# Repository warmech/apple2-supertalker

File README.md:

# Supertalker - A Speech Digitizer for the Apple II

The Supertalker is a speech digitizer card for the Apple II by Mountain Computer, Inc. Originally produced in 1979 (and subsequently for the PC in the 1980s), the Supertalker is capable of digitizing and playing back speech at any of four bitrates: 0.5 KBps, 1 KBps, 2 KBps, and 4 KBps. The kit originally included a microphone and enclosed (in woodgrain, no less) speaker for use with the card.

This card is somewhat hard to find now, but I happened to come across one at a recent retrocomputing meetup for a few bucks (not knowing what it was other than some cursory googling at the time) and wanted to preserve it. The included manual and disk images are care of [apple2.org](https://mirrors.apple2.org.za/Apple%20II%20Documentation%20Project/Interface%20Cards/Speech/Mountain%20Computer%20Supertalker/).

More details to follow once initial assembly and testing are completed.

## Errata

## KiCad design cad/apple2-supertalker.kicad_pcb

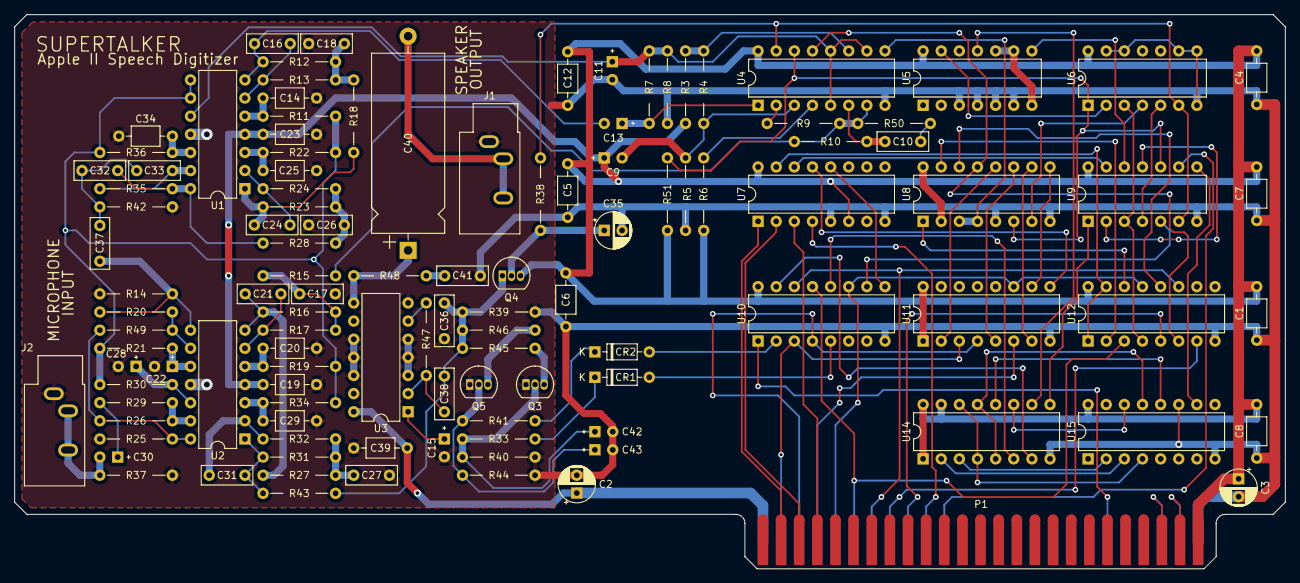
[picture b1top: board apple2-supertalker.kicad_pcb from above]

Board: 2 copper layers, 178.0 x 77.6 mm, 114 parts (0 on the bottom side), 106 nets.

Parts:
C1, C4, C5, C6, C7, C8, C12, C14, C19, C20, C23, C25, C29, C34, C39: 0.1uF 50V; C_Axial_L3.8mm_D2.6mm_P7.50mm_Horizontal
C2, C3, C35: 10uF 35V; CP_Radial_D5.0mm_P2.50mm
C9: 0.39uF 50V; CP_Radial_Tantal_D4.5mm_P2.50mm
C10: 0.068uF 63V; C_Rect_L7.0mm_W2.5mm_P5.00mm
C11, C13, C15, C22, C28, C30, C42, C43: 10uF 25V; CP_Radial_Tantal_D4.5mm_P2.50mm
C16, C31: 0.0015uF 100V; C_Rect_L7.0mm_W2.5mm_P5.00mm
C17, C18, C26, C27, C32, C33, C37, C38, C41: 0.01uF 100V; C_Rect_L7.0mm_W2.5mm_P5.00mm
C21, C24: 82pF 500V; C_Rect_L7.0mm_W2.5mm_P5.00mm
C36: 100pF 500V; C_Rect_L7.0mm_W2.5mm_P5.00mm
C40: 470uF 25V; CP_Axial_L25.0mm_D10.0mm_P30.00mm_Horizontal
CR1, CR2: 1N4148; D_DO-35_SOD27_P7.62mm_Horizontal
J1: SPKR OUTPUT; Jack_3.5mm_CUI_SJ1-3533NG_Horizontal
J2: MIC INPUT; Jack_3.5mm_CUI_SJ1-3533NG_Horizontal
P1: Apple II Expansion Bus; Apple_II_Expansion_Bus_Card_Edge
Q3, Q4, Q5: PN2222A; TO-92_Inline
R3: 3.3K; R_Axial_DIN0207_L6.3mm_D2.5mm_P10.16mm_Horizontal
R4: 18K; R_Axial_DIN0207_L6.3mm_D2.5mm_P10.16mm_Horizontal
R5: 2.7M; R_Axial_DIN0207_L6.3mm_D2.5mm_P10.16mm_Horizontal
R6: 1.3K; R_Axial_DIN0207_L6.3mm_D2.5mm_P10.16mm_Horizontal
R7, R9: 620; R_Axial_DIN0207_L6.3mm_D2.5mm_P10.16mm_Horizontal
R8, R29, R37, R49, R51: 1K; R_Axial_DIN0207_L6.3mm_D2.5mm_P10.16mm_Horizontal
R10, R38: 4.7K; R_Axial_DIN0207_L6.3mm_D2.5mm_P10.16mm_Horizontal
R11, R14, R19, R21, R22, R25, R30, R33, R34, R36, R41: 10K; R_Axial_DIN0207_L6.3mm_D2.5mm_P10.16mm_Horizontal
R12, R18, R27, R31, R42: 20K; R_Axial_DIN0207_L6.3mm_D2.5mm_P10.16mm_Horizontal
R13, R32: 33K; R_Axial_DIN0207_L6.3mm_D2.5mm_P10.16mm_Horizontal
R15, R16, R23, R28: 51K; R_Axial_DIN0207_L6.3mm_D2.5mm_P10.16mm_Horizontal
R17, R24, R43: 62K; R_Axial_DIN0207_L6.3mm_D2.5mm_P10.16mm_Horizontal
R20: 22K; R_Axial_DIN0207_L6.3mm_D2.5mm_P10.16mm_Horizontal
R26: 15K; R_Axial_DIN0207_L6.3mm_D2.5mm_P10.16mm_Horizontal
R35: 150K; R_Axial_DIN0207_L6.3mm_D2.5mm_P10.16mm_Horizontal
R39: 9.1K; R_Axial_DIN0207_L6.3mm_D2.5mm_P10.16mm_Horizontal
R40, R44: 6.2K; R_Axial_DIN0207_L6.3mm_D2.5mm_P10.16mm_Horizontal
R45: 2.2K; R_Axial_DIN0207_L6.3mm_D2.5mm_P10.16mm_Horizontal
R46: 6.8K; R_Axial_DIN0207_L6.3mm_D2.5mm_P10.16mm_Horizontal
R47: 470K; R_Axial_DIN0207_L6.3mm_D2.5mm_P10.16mm_Horizontal
R48: 2.7K; R_Axial_DIN0207_L6.3mm_D2.5mm_P10.16mm_Horizontal
R50: 68; R_Axial_DIN0207_L6.3mm_D2.5mm_P10.16mm_Horizontal
U1, U2: LM324; DIP-14_W7.62mm
U3: LM380N; DIP-14_W7.62mm
U4: MC3418; DIP-16_W7.62mm
U5: 4013; DIP-14_W7.62mm
U6: 4001; DIP-14_W7.62mm
U7: 74LS138; DIP-16_W7.62mm
U8: 4035; DIP-16_W7.62mm
U9: 74LS04; DIP-14_W7.62mm
U10, U11: 74LS174; DIP-16_W7.62mm
U12: 74LS367; DIP-16_W7.62mm
U14: 4529; DIP-16_W7.62mm
U15: 4040; DIP-16_W7.62mm

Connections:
+5V: C1.2, C3.1, C4.2, C5.2, C6.2, C7.2, C8.2, C9.1, C12.2, C19.2, C23.2, P1.25 (+5V), Q4.3 (C), R3.2, R6.2, R51.2, U1.4 (V+), U2.4 (V+), U4.16 (VCC), U5.14 (VDD), U6.14 (VDD), U7.6 (E3), U7.16 (VCC), U8.2 (TC), U8.16 (VCC), U9.14 (VCC), U10.16 (VCC), U11.1 (~Mr), U11.16 (VCC), U12.16 (VCC), U14.1 (STX), U14.15 (STY), U14.16 (VDD), U15.16 (VDD)
+12V: C2.1, C39.2, P1.50 (+12V), U3.14 (VS)
/ANALOG OUT: R9.1, R10.2, R15.1, R50.2, U4.7 (AO)
/WRITE STATUS: U7.12 (O3), U10.9 (Cp)
A0: P1.2 (A0), U7.1 (A0)
A1: P1.3 (A1), U7.2 (A1)
A2: P1.4 (A2), U7.3 (A2)
D0: P1.49 (D0), U10.3 (D0), U11.3 (D0)
D1: P1.48 (D1), U10.4 (D1), U11.4 (D1)
D2: P1.47 (D2), U11.6 (D2)
D3: P1.46 (D3), U10.11 (D3), U11.11 (D3), U12.13
D4: P1.45 (D4), U10.13 (D4), U12.3
D5: P1.44 (D5), U10.14 (D5), U12.11
D6: P1.43 (D6), U12.7
D7: P1.42 (D7), U12.5
GND: C1.1, C2.2, C3.2, C4.1, C5.1, C6.1, C7.1, C8.1, C11.2, C12.1, C14.1, C15.2, C17.1, C18.1, C19.1, C20.2, C22.2, C23.1, C25.1, C26.1, C27.1, C28.2, C29.2, C34.1, C35.2, C36.1, C39.1, C41.1, C42.2, C43.2, J1.S, J2.S, P1.26 (GND), Q3.1 (E), Q5.1 (E), R5.1, R8.1, R14.2, R25.2, R37.2, R39.2, R40.2, R42.2, R44.2, U1.11 (V-), U2.11 (V-), U3.3 (GND), U3.4 (GND), U3.5 (GND), U3.7 (GND), U3.10 (GND), U3.11 (GND), U3.12 (GND), U4.8 (GND), U5.3 (C), U5.4 (R), U5.5 (D), U5.6 (S), U5.7 (VSS), U5.9 (D), U5.10 (R), U6.7 (VSS), U6.8, U6.9, U6.12, U6.13, U7.5 (E2), U7.8 (GND), U8.5 (RESET), U8.8 (GND), U9.7 (GND), U10.8 (GND), U11.8 (GND), U12.8 (GND), U14.8 (VSS), U15.8 (VSS), U15.11 (Reset)
unnamed: C10.1, R50.1
unnamed: C13.2, C16.2, R12.2, U1.7
unnamed: C17.2, R15.2, R16.1, R17.1
unnamed: C18.2, R12.1, R13.1, R18.2
unnamed: C21.2, R16.2, R27.1, U2.7
unnamed: C24.2, R18.1, R23.2, U1.1
unnamed: C26.2, R23.1, R24.1, R28.2
unnamed: C27.2, R27.2, R31.1, R32.1
unnamed: C30.1, R29.1
unnamed: C30.2, J2.R, J2.T, R37.1
unnamed: C31.2, R31.2, R43.1, U2.1
unnamed: C32.1, C33.1, C37.2, R42.1
unnamed: C32.2, R28.1, R35.1, U1.14
unnamed: C37.1, R14.1, R20.1, U2.8
unnamed: C40.1, R48.1, U3.8
unnamed: C40.2, J1.R, J1.T
unnamed: C41.2, R48.2
unnamed: CR1.2 (A), U10.5 (Q1)
unnamed: CR1.1 (K), R33.1
unnamed: CR2.2 (A), U10.2 (Q0)
unnamed: CR2.1 (K), R41.1
unnamed: P1.24 (/DMAOUT), P1.27 (/DMAIN)
unnamed: P1.23 (/INTOUT), P1.28 (/INTIN)
unnamed: C42.1, Q3.2 (B), R33.2, R40.1
unnamed: Q3.3 (C), R45.1
unnamed: C35.1, Q4.2 (B), R38.2
unnamed: C36.2, C38.2, Q4.1 (E), R39.1, R43.2, R45.2, R46.2
unnamed: C43.1, Q5.2 (B), R41.2, R44.1
unnamed: Q5.3 (C), R46.1
unnamed: R25.1, R26.2, R49.1, U2.14
unnamed: C25.2, R22.1, U1.3 (+)
unnamed: C24.1, R24.2, U1.2 (-)
unnamed: C14.2, R11.1, U1.5 (+)
unnamed: C16.1, R13.2, U1.6 (-)
unnamed: C11.1, R7.1, R8.2, U1.10 (+), U4.5 (RI), U4.10 (REF), U4.12 (DT)
unnamed: R11.2, R19.2, R21.2, R22.2, R30.2, R34.2, R36.2, U1.8, U1.9 (-)
unnamed: C34.2, R36.1, U1.12 (+)
unnamed: C33.2, R35.2, U1.13 (-)
unnamed: C29.1, R34.1, U2.3 (+)
unnamed: C31.1, R32.2, U2.2 (-)
unnamed: C20.1, R19.1, U2.5 (+)
unnamed: C21.1, R17.2, U2.6 (-)
unnamed: C22.1, R21.1, U2.10 (+)
unnamed: R20.2, R49.2, U2.9 (-)
unnamed: C28.1, R30.1, U2.12 (+)
unnamed: R26.1, R29.2, U2.13 (-)
unnamed: C38.1, R47.1, U3.2 (+)
unnamed: R47.2, U3.6 (-)
unnamed: C15.1, U3.1 (BYPASS)
unnamed: R9.2, U4.2 (AF)
unnamed: C13.1, R7.2, U4.1 (AI)
unnamed: R51.1, U4.14 (CLK), U6.1, U8.6 (CLK), U9.10
unnamed: U4.13 (DI), U8.13 (Q4), U12.6
unnamed: U4.9 (DO), U8.3 (/K), U8.4 (J)
unnamed: R38.1, U4.15 (E/D), U6.6, U9.6
unnamed: C10.2, R10.1, U4.6 (FI)
unnamed: R6.1, U4.4 (GC)
unnamed: C9.2, R4.1, R5.2, U4.3 (SF)
unnamed: R3.1, R4.2, U4.11 (/CO)
unnamed: U5.13 (Q), U6.2
unnamed: U5.8 (S), U9.12
unnamed: U6.5, U9.4
unnamed: U7.14 (O1), U9.13
unnamed: U6.4, U8.7 (PSC)
unnamed: U8.1 (Q1), U12.14
unnamed: U8.15 (Q2), U12.2
unnamed: U8.14 (Q3), U12.12
unnamed: U9.2, U9.11
unnamed: U9.5, U10.10 (Q3)
unnamed: U10.12 (Q4), U14.6 (A)
unnamed: U10.15 (Q5), U14.7 (B)
unnamed: U8.12 (PI4), U11.2 (Q0)
unnamed: U8.11 (PI3), U11.5 (Q1)
unnamed: U8.10 (PI2), U11.7 (Q2)
unnamed: U8.9 (PI1), U11.10 (Q3)
unnamed: U6.3, U9.3, U12.4
unnamed: U5.11 (C), U14.10 (W)
unnamed: U14.2 (X0), U15.3 (Q4)
unnamed: U14.3 (X1), U15.2 (Q5)
unnamed: U14.4 (X2), U14.14 (Y0), U15.4 (Q6)
unnamed: U14.5 (X3), U14.13 (Y1), U15.13 (Q7)
unnamed: U14.12 (Y2), U15.12 (Q8)
unnamed: U14.11 (Y3), U15.14 (Q9)
unnamed: U9.1, U14.9 (Z)
unnamed: U9.8, U15.10 (CLK)
READ_DATA: U7.15 (O0), U12.1, U12.15
WRITE_DATA: U7.13 (O2), U11.9 (Cp)
/DEVSEL: P1.41 (/DEVSEL), U7.4 (E1)
/RESET: P1.31 (/RES), U10.1 (~Mr)
Φ0: P1.40 (Φ0), U9.9

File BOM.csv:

Item,Qty,Reference(s),Value,LibPart,Footprint,Datasheet,DNP,Sim.Device,Sim.Pins
1,15,"C1, C4, C5, C6, C7, C8, C12, C14, C19, C20, C23, C25, C29, C34, C39",0.1uF 50V,Device:C,Capacitor_THT:C_Axial_L3.8mm_D2.6mm_P7.50mm_Horizontal,~,,,
2,3,"C2, C3, C35",10uF 35V,Device:C_Polarized_US,Capacitor_THT:CP_Radial_D5.0mm_P2.50mm,~,,,
3,1,C9,0.39uF 50V,Device:C_Polarized_US,Capacitor_THT_Custom:CP_Radial_Tantal_D4.5mm_P2.50mm,~,,,
4,1,C10,0.068uF 63V,Device:C,Capacitor_THT:C_Rect_L7.0mm_W2.5mm_P5.00mm,PolyFilm,,,
5,8,"C11, C13, C15, C22, C28, C30, C42, C43",10uF 25V,Device:C_Polarized_US,Capacitor_THT_Custom:CP_Radial_Tantal_D4.5mm_P2.50mm,~,,,
6,2,"C16, C31",0.0015uF 100V,Device:C,Capacitor_THT:C_Rect_L7.0mm_W2.5mm_P5.00mm,PolyFilm,,,
7,9,"C17, C18, C26, C27, C32, C33, C37, C38, C41",0.01uF 100V,Device:C,Capacitor_THT:C_Rect_L7.0mm_W2.5mm_P5.00mm,PolyFilm,,,
8,2,"C21, C24",82pF 500V,Device:C,Capacitor_THT:C_Rect_L7.0mm_W2.5mm_P5.00mm,PolyFilm,,,
9,1,C36,100pF 500V,Device:C,Capacitor_THT:C_Rect_L7.0mm_W2.5mm_P5.00mm,PolyFilm,,,
10,1,C40,470uF 25V,Device:C_Polarized_US,Capacitor_THT:CP_Axial_L25.0mm_D10.0mm_P30.00mm_Horizontal,~,,,
11,2,"CR1, CR2",1N4148,Diode:1N4148,Diode_THT:D_DO-35_SOD27_P7.62mm_Horizontal,https://assets.nexperia.com/documents/data-sheet/1N4148_1N4448.pdf,,D,1=K 2=A
12,1,J1,SPKR OUTPUT,Connector_Audio:AudioJack3,Connector_Audio:Jack_3.5mm_CUI_SJ1-3533NG_Horizontal,~,,,
13,1,J2,MIC INPUT,Connector_Audio:AudioJack3,Connector_Audio:Jack_3.5mm_CUI_SJ1-3533NG_Horizontal,~,,,
14,1,P1,Apple II Expansion Bus,Connector_Custom:Apple_II_Expansion_Bus,Connector_Custom:Apple_II_Expansion_Bus_Card_Edge,,,,
15,3,"Q3, Q4, Q5",PN2222A,Transistor_BJT:PN2222A,Package_TO_SOT_THT:TO-92_Inline,https://www.onsemi.com/pub/Collateral/PN2222-D.PDF,,,
16,1,R3,3.3K,Device:R_US,Resistor_THT_Custom:R_Axial_DIN0207_L6.3mm_D2.5mm_P10.16mm_Horizontal,~,,,
17,1,R4,18K,Device:R_US,Resistor_THT_Custom:R_Axial_DIN0207_L6.3mm_D2.5mm_P10.16mm_Horizontal,~,,,
18,1,R5,2.7M,Device:R_US,Resistor_THT_Custom:R_Axial_DIN0207_L6.3mm_D2.5mm_P10.16mm_Horizontal,~,,,
19,1,R6,1.3K,Device:R_US,Resistor_THT_Custom:R_Axial_DIN0207_L6.3mm_D2.5mm_P10.16mm_Horizontal,~,,,
20,2,"R7, R9",620,Device:R_US,Resistor_THT_Custom:R_Axial_DIN0207_L6.3mm_D2.5mm_P10.16mm_Horizontal,~,,,
21,5,"R8, R29, R37, R49, R51",1K,Device:R_US,Resistor_THT_Custom:R_Axial_DIN0207_L6.3mm_D2.5mm_P10.16mm_Horizontal,~,,,
22,2,"R10, R38",4.7K,Device:R_US,Resistor_THT_Custom:R_Axial_DIN0207_L6.3mm_D2.5mm_P10.16mm_Horizontal,~,,,
23,11,"R11, R14, R19, R21, R22, R25, R30, R33, R34, R36, R41",10K,Device:R_US,Resistor_THT_Custom:R_Axial_DIN0207_L6.3mm_D2.5mm_P10.16mm_Horizontal,~,,,
24,5,"R12, R18, R27, R31, R42",20K,Device:R_US,Resistor_THT_Custom:R_Axial_DIN0207_L6.3mm_D2.5mm_P10.16mm_Horizontal,~,,,
25,2,"R13, R32",33K,Device:R_US,Resistor_THT_Custom:R_Axial_DIN0207_L6.3mm_D2.5mm_P10.16mm_Horizontal,~,,,
26,4,"R15, R16, R23, R28",51K,Device:R_US,Resistor_THT_Custom:R_Axial_DIN0207_L6.3mm_D2.5mm_P10.16mm_Horizontal,~,,,
27,3,"R17, R24, R43",62K,Device:R_US,Resistor_THT_Custom:R_Axial_DIN0207_L6.3mm_D2.5mm_P10.16mm_Horizontal,~,,,
28,1,R20,22K,Device:R_US,Resistor_THT_Custom:R_Axial_DIN0207_L6.3mm_D2.5mm_P10.16mm_Horizontal,~,,,
29,1,R26,15K,Device:R_US,Resistor_THT_Custom:R_Axial_DIN0207_L6.3mm_D2.5mm_P10.16mm_Horizontal,~,,,
30,1,R35,150K,Device:R_US,Resistor_THT_Custom:R_Axial_DIN0207_L6.3mm_D2.5mm_P10.16mm_Horizontal,~,,,
31,1,R39,9.1K,Device:R_US,Resistor_THT_Custom:R_Axial_DIN0207_L6.3mm_D2.5mm_P10.16mm_Horizontal,~,,,
32,2,"R40, R44",6.2K,Device:R_US,Resistor_THT_Custom:R_Axial_DIN0207_L6.3mm_D2.5mm_P10.16mm_Horizontal,~,,,
33,1,R45,2.2K,Device:R_US,Resistor_THT_Custom:R_Axial_DIN0207_L6.3mm_D2.5mm_P10.16mm_Horizontal,~,,,
34,1,R46,6.8K,Device:R_US,Resistor_THT_Custom:R_Axial_DIN0207_L6.3mm_D2.5mm_P10.16mm_Horizontal,~,,,
35,1,R47,470K,Device:R_US,Resistor_THT_Custom:R_Axial_DIN0207_L6.3mm_D2.5mm_P10.16mm_Horizontal,~,,,
36,1,R48,2.7K,Device:R_US,Resistor_THT_Custom:R_Axial_DIN0207_L6.3mm_D2.5mm_P10.16mm_Horizontal,~,,,
37,1,R50,68,Device:R_US,Resistor_THT_Custom:R_Axial_DIN0207_L6.3mm_D2.5mm_P10.16mm_Horizontal,~,,,
38,2,"U1, U2",LM324,Amplifier_Operational:LM324,Package_DIP:DIP-14_W7.62mm,http://www.ti.com/lit/ds/symlink/lm2902-n.pdf,,,
39,1,U3,LM380N,Amplifier_Audio:LM380N,Package_DIP:DIP-14_W7.62mm,http://www.ti.com/lit/ds/symlink/lm380.pdf,,,
40,1,U4,MC3418,Interface_Custom:MC3418,Package_DIP:DIP-16_W7.62mm,,,,
41,1,U5,4013,4xxx:4013,Package_DIP:DIP-14_W7.62mm,http://www.onsemi.com/pub/Collateral/MC14013B-D.PDF,,,
42,1,U6,4001,4xxx:4001,Package_DIP:DIP-14_W7.62mm,http://www.intersil.com/content/dam/Intersil/documents/cd40/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,,,
43,1,U7,74LS138,74xx:74LS138,Package_DIP:DIP-16_W7.62mm,http://www.ti.com/lit/gpn/sn74LS138,,,
44,1,U8,4035,4xxx_Custom:4035,Package_DIP:DIP-16_W7.62mm,,,,
45,1,U9,74LS04,74xx:74LS04,Package_DIP:DIP-14_W7.62mm,http://www.ti.com/lit/gpn/sn74LS04,,,
46,1,U10,74LS174,:74LS174_1,Package_DIP:DIP-16_W7.62mm,http://www.ti.com/lit/gpn/sn74LS174,,,
47,1,U11,74LS174,74xx:74LS174,Package_DIP:DIP-16_W7.62mm,http://www.ti.com/lit/gpn/sn74LS174,,,
48,1,U12,74LS367,:74LS367_4,Package_DIP:DIP-16_W7.62mm,,,,
49,1,U14,4529,4xxx_IEEE:4529,Package_DIP:DIP-16_W7.62mm,,,,
50,1,U15,4040,4xxx:4040,Package_DIP:DIP-16_W7.62mm,http://www.intersil.com/content/dam/Intersil/documents/cd40/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,,,
